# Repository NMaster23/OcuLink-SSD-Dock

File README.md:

# OcuLink-SSD-Dock
This is an oculink dock designed for SSD'S kind of like a cartridge system.

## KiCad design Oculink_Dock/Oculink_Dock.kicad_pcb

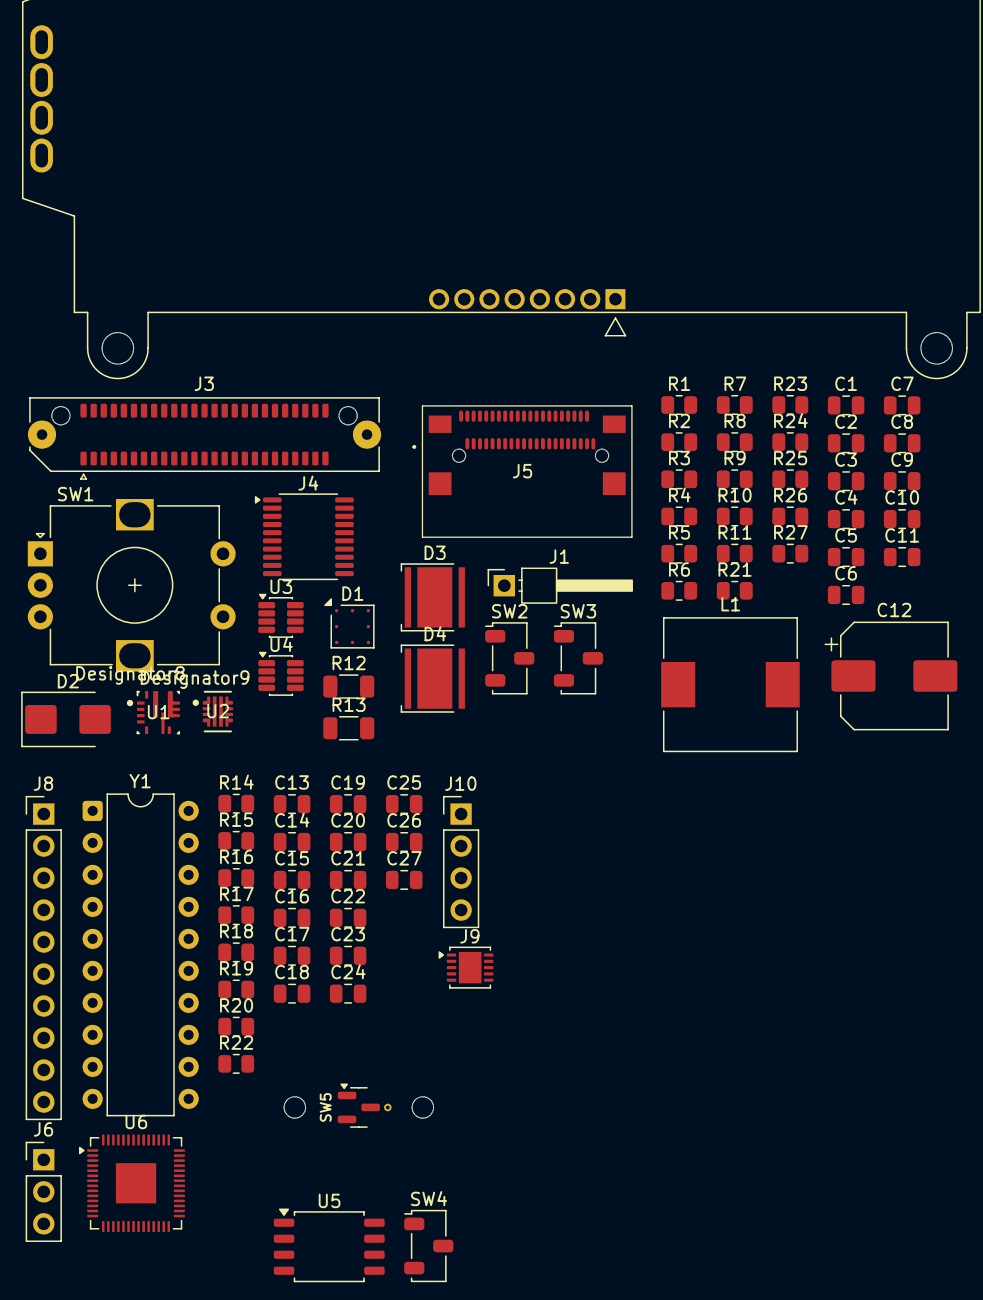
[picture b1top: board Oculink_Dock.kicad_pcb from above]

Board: 2 copper layers, 80 parts (0 on the bottom side), 85 nets, no tracks yet.

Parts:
C1, C2: 10uF; C_0805_2012Metric
C3, C8: 100nF; C_0805_2012Metric
C4: 22nF; C_0805_2012Metric
C5, C14, C19, C27: 1uF; C_0805_2012Metric
C6: 2.2nF; C_0805_2012Metric
C7: 3300pF; C_0805_2012Metric
C9: 150pF; C_0805_2012Metric
C10, C11: 15uF; C_0805_2012Metric
C12: 470uF; CP_Elec_8x10
C13, C17, C18, C20, C21, C22, C23, C24, C25, C26: 0.1uF; C_0805_2012Metric
C15, C16: 15pF; C_0805_2012Metric
D1: D_Zener; OnSemi_ODCSP8_BGA-8_3.16x3.16mm_Layout3x3_P1.26mm
D2: D_Schottky; D_SMB
D3, D4: LED; LED_Cree-XHP50_3V_HighDensity
J1: Prsnc; PinHeader_1x01_P2.54mm_Horizontal
J2: Screen; NHD-C0220BiZ-FSRGB
J3: ERF8-025-XX-X-D-RA-L-XX; Samtec_ERF8-025-XX.X-DV-L_2x25_P0.8mm_Socket_Latch
J4: DIN-4; TSSOP-20_4.4x6.5mm_P0.65mm
J5: 1719820142
J6: Conn_01x03; PinHeader_1x03_P2.54mm_Vertical
J8: Conn_01x10; PinHeader_1x10_P2.54mm_Vertical
J9: USB_C_Receptacle_USB2.0_14P; WDFN-10-1EP_3x3mm_P0.5mm_EP1.8x2.5mm
J10: Conn_01x04; PinHeader_1x04_P2.54mm_Vertical
L1: 2.2uH; L_10.4x10.4_H4.8
R1: 59k; R_0805_2012Metric
R2: 390k; R_0805_2012Metric
R3: 52.3k; R_0805_2012Metric
R4: 470k; R_0805_2012Metric
R5, R6: 100k; R_0805_2012Metric
R7: 45.3k; R_0805_2012Metric
R8, R17, R22: 10k; R_0805_2012Metric
R9: 549; R_0805_2012Metric
R10: 47k; R_0805_2012Metric
R11: 5.6k; R_0805_2012Metric
R12, R13: 0.03; R_1206_3216Metric
R14, R18: 1k; R_0805_2012Metric
R15, R16: 27; R_0805_2012Metric
R19, R20: 5.1k; R_0805_2012Metric
R21, R23, R24, R25, R26, R27: 2.2k; R_0805_2012Metric
SW1: RotaryEncoder_Switch; RotaryEncoder_Alps_EC12E-Switch_Vertical_H20mm
SW2: Eject; Nidec_Copal_CAS-120A
SW3: Rescan; Nidec_Copal_CAS-120A
SW4: SW_Push; Nidec_Copal_CAS-120A
SW5: SW_Push; SW_MX_HE_0deg_1u
U1: TPS56A37RPAR; RPA0010A-MFG
U2: TPS259470ARPWR; RPW0010A-MFG
U3, U4: INA219BxDCN; SOT-23-8
U5: W25Q128JVS; SOIC-8_5.3x5.3mm_P1.27mm
U6: RP2040; QFN-56-1EP_7x7mm_P0.4mm_EP3.2x3.2mm
Y1: 12 MHz; DIP-20_W7.62mm

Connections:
+1V1: C14.1, C17.1, C18.1, U6.23 (DVDD), U6.45 (VREG_VOUT), U6.50 (DVDD)
+3V3: C13.1, C19.1, C20.1, C21.1, C22.1, C23.1, C24.1, C25.1, C26.1, C27.1, J2.1, J3.38, R5.2, R6.2, R12.2, R17.1, R22.1, R23.1, R24.1, R25.1, R26.1, R27.1, U3.1 (IN+), U3.4 (VS), U4.4 (VS), U4.8 (A1), U5.8 (VCC), U6.1 (IOVDD), U6.10 (IOVDD), U6.22 (IOVDD), U6.33 (IOVDD), U6.42 (IOVDD), U6.43 (ADC_AVDD), U6.44 (VREG_VIN), U6.48 (USB_VDD), U6.49 (IOVDD)
+12V: C1.1, C2.1, C3.1, C5.1, J4.1, J4.4, R4.1, U1.8 (VIN), U2.5 (IN)
A0: J8.7, U6.38 (GPIO26/ADC0)
A1: J8.8, U6.39 (GPIO27/ADC1)
A2: J8.9, U6.40 (GPIO28/ADC2)
A3: J8.10, U6.41 (GPIO29/ADC3)
BP_TYPE: J3.14, J5.B9
CLK: J3.17, J5.A9
CPRSNT: J3.25, J5.A13
CWAKE: J3.16, J5.B10
DATA: J3.19, J5.A10
G0: R5.1, U1.4 (PG), U6.2 (GPIO0)
G1: R6.1, U2.3 (PG), U6.3 (GPIO1)
G2: SW3.2, U6.4 (GPIO2)
G3: SW2.2, U6.5 (GPIO3)
G4: R24.2, R27.2, U3.6 (SDA), U4.6 (SDA), U6.6 (GPIO4)
G5: R25.2, R26.2, U3.5 (SCL), U4.5 (SCL), U6.7 (GPIO5)
G6: J1.1 (Pin_1_1), U6.8 (GPIO6)
G7: J10.1, U6.9 (GPIO7)
G8: J10.2, U6.11 (GPIO8)
G9: J2.5, U6.12 (GPIO9)
G10: J2.3, U6.13 (GPIO10)
G11: J2.4, U6.14 (GPIO11)
G12: J2.6, U6.15 (GPIO12)
G13: J2.7, U6.16 (GPIO13)
G14: J2.8, U6.17 (GPIO14)
G15: SW1.A, U6.18 (GPIO15)
G16: SW1.B, U6.27 (GPIO16)
G17: SW1.S1, U6.28 (GPIO17)
G18: J10.3, U6.29 (GPIO18)
G19: J10.4, U6.30 (GPIO19)
G20: J8.1, U6.31 (GPIO20)
G21: J8.2, U6.32 (GPIO21)
G22: J8.3, U6.34 (GPIO22)
G23: J8.4, U6.35 (GPIO23)
G24: J8.5, U6.36 (GPIO24)
G25: J8.6, U6.37 (GPIO25)
GND: C1.2, C2.2, C3.2, C4.2, C5.2, C6.2, C7.2, C9.1, C10.1, C10.2, C11.1, C11.2, C12.2, C13.2, C14.2, C15.1, C16.1, C17.2, C18.2, C19.2, C20.2, C21.2, C22.2, C23.2, C24.2, C25.2, C26.2, C27.2, D2.2 (A), D3.1 (K), D4.1 (K), J2.2, J3.12, J3.15, J3.18, J3.21, J3.24, J3.27, J3.30, J3.33, J3.36, J3.39, J3.40, J3.45, J3.46, J4.2, J4.3, J5.A2, J5.A5, J5.A8, J5.A11, J5.A14, J5.A17, J5.A20, J5.B2, J5.B5, J5.B8, J5.B11, J5.B14, J5.B17, J5.B20, J5.MP1, J5.MP2, J5.MP3, J5.MP4, J6.2, L1.2, R1.1, R2.1, R3.2, R7.2, R8.1, R9.2, R11.2, R12.1, R19.2, R20.2, SW1.C, SW1.S2, SW2.1, SW3.1, SW4.1, SW5.1, U1.3 (AGND), U1.9 (PGND), U2.8 (GND), U3.2 (IN-), U3.3 (GND), U3.7 (A0), U3.8 (A1), U4.3 (GND), U4.7 (A0), U5.4 (GND), U6.19 (TESTEN), U6.57 (GND), Y1.2 (G), Y1.4 (G)
unnamed: C16.2, R18.1, Y1.1
unnamed: C12.1, D2.1 (K), R10.1, R13.2, U2.6 (OUT), U4.2 (IN-)
unnamed: D3.2 (A), R21.2
unnamed: D4.2 (A), R23.2
unnamed: R14.1, SW4.2
unnamed: C8.1, U1.7 (BOOT)
unnamed: C9.2, R7.1, R8.2, U1.2 (FB)
unnamed: R3.1, U1.10 (MODE)
unnamed: C4.1, U1.5 (SS)
unnamed: C8.2, L1.1, U1.6 (SW)
unnamed: R1.2, R4.2, U2.1 (EN_UVLO)
unnamed: R9.1, U2.9 (ILM)
unnamed: C6.1, U2.10 (ITIMER)
unnamed: R2.2, U2.2 (OVCSEL)
unnamed: R10.2, R11.1, U2.4 (PGTH)
unnamed: C7.1, U2.7 (dVdt)
unnamed: R22.2, SW5.2, U6.26 (RUN)
unnamed: R15.2, U6.46 (USB_DM)
unnamed: R16.2, U6.47 (USB_DP)
O_3v3: J5.A1, J5.B21
O_5v: J5.A21, J5.B1
PCIe_PWR: J3.41, J3.42, J3.43, J3.44, J3.47, J3.48, J3.49, J3.50, R13.1, U4.1 (IN+)
PERST: J3.23, J5.A12
Q_SCLK: U5.6 (CLK), U6.52 (QSPI_SCLK)
Q_SD0: U5.5 (DI/IO_{0}), U6.53 (QSPI_SD0)
Q_SD1: U5.2 (DO/IO_{1}), U6.55 (QSPI_SD1)
Q_SD2: U5.3 (~WP/IO_{2}), U6.54 (QSPI_SD2)
Q_SD3: U5.7 (~HOLD/~RESET/IO_{3}), U6.51 (QSPI_SD3)
Q_SS: R14.2, R17.2, U5.1 (~CS), U6.56 (~QSPI_SS)
REFCLK+: J3.20, J5.B12
REFCLK-: J3.22, J5.B13
RX1+: J3.11, J5.A6
RX1-: J3.13, J5.A7
RX2+: J3.29, J5.A15
RX2-: J3.31, J5.A16
RX3+: J3.35, J5.A18
RX3-: J3.37, J5.A19
SWCLK: J6.1, U6.24 (SWCLK)
SWDIO: J6.3, U6.25 (SWDIO)
TX1-: J3.10, J5.B7
TX2+: J3.26, J5.B15
TX2-: J3.28, J5.B16
TX3+: J3.32, J5.B18
TX3-: J3.34, J5.B19
XIN: C15.2, U6.20 (XIN), Y1.3
XOUT: R18.2, U6.21 (XOUT)
